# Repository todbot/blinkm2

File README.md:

blinkm_mk2
==========

## aka. BlinkM2, aka BlinkM as WS2812 / NeoPixel controller

### Key Features
* WS2812 / NeoPixel controller (of at least 16 pixels)
* On-board LEDs (maybe two or more)
* Small! (< 1 inch square)
* Stand-alone operation, as original BlinkM
* Inputs for controlling behavior
* Turn into tiny Arduino! (attiny85, attiny84)
* Default firmware is just Arduino sketch (uses awesome ATtinyCore)

### How is this different from blink(1) USB RGB LED?
* blink(1) is retail product, not programmable, tied to a computer, with more robust USB stack
* BlinkM2 / BlinkM Neo is a tiny Arduino, meant to work stand-alone

### Some future directions
* Connector for additional Neopixel LEDs (not just pads)
* USB-based? NO (Micronuclues bootloader, like Digispark), NOT I2C? (but could use A0)
* Serial as well as I2C?  Maybe with SoftSerial
* Should on-board LEDs be in-line or parallel to off-board?
* Can we switch them? (Need more pins then, no ATtiny85)
- Digispark based?
- events trigger patterns:
- CapSense using "ADCTouch" library  (can this work on ATtiny84/85 system?)
- put inbound resistor on inputs for protection?

### Notes:
- TinyTouchLib works on Digispark (ATtiny85 at 16.5MHZ), with light editing. See TinyTouchTest1 sketch

### Further Reading:
- See also PatternIdeas.md

-
-

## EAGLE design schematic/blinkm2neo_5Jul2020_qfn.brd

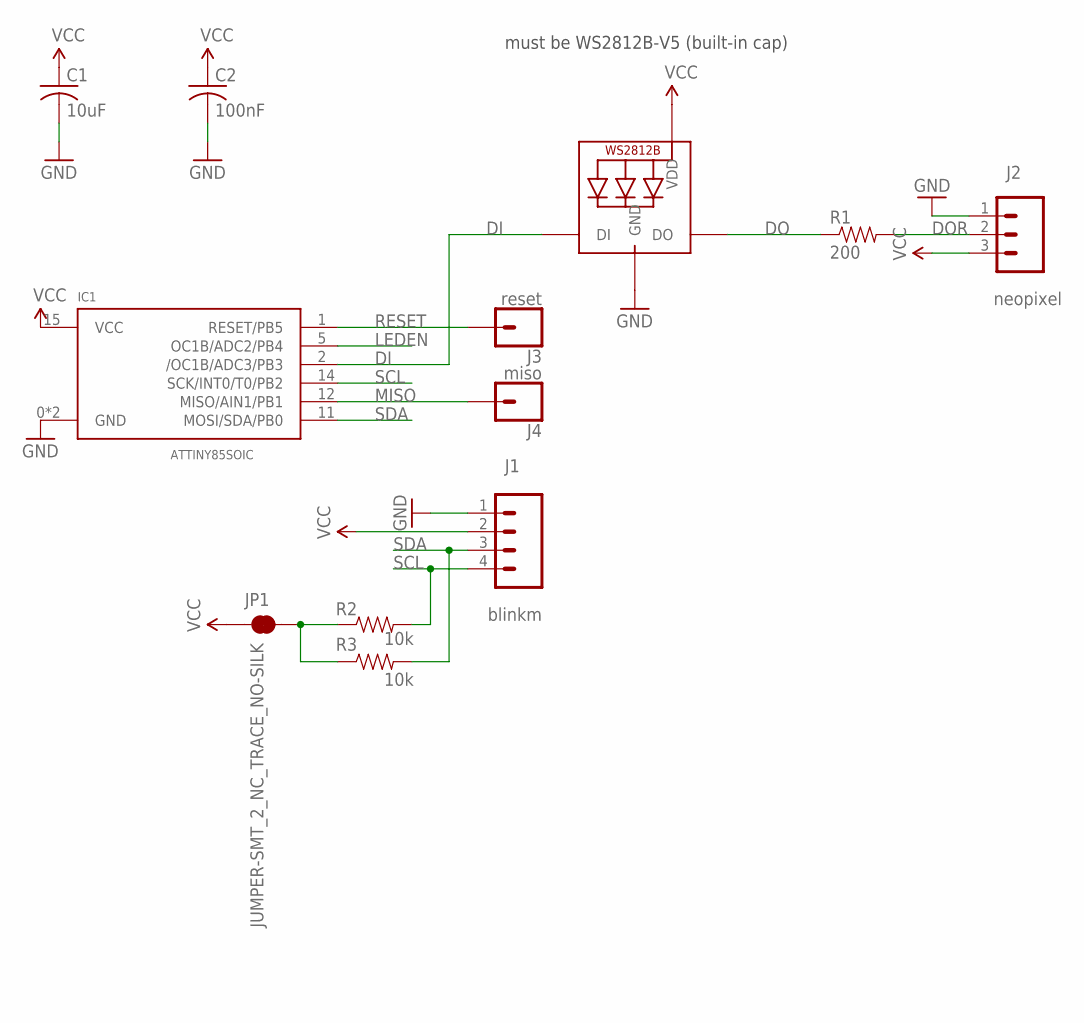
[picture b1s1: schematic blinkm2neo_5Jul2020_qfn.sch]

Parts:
C1: 10uF; C0402
C2: 100nF; C0402
IC1: ATTINY85SOIC; QFN20
J1: blinkm; 1X04
J2: neopixel; 1X03
J3: reset; 1X01_NO_SILK
J4: miso; 1X01_NO_SILK
JP1: JUMPER-SMT_2_NC_TRACE_NO-SILK; SMT-JUMPER_2_NC_TRACE_NO-SILK
LED1: WS2812B-V5; WS2812B
R1: 200; 0402
R2, R3: 10k; 0402

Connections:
DI: IC1.2 (/OC1B/ADC3/PB3), LED1.4-DIN (DI)
DO: LED1.2-DOUT (DO), R1.1
DOR: J2.2, R1.2
GND: C1.2, C2.2, IC1.0 (GND), IC1.8 (GND), J1.1, J2.1, LED1.3-GND (GND)
LEDEN: IC1.5 (OC1B/ADC2/PB4)
MISO: IC1.12 (MISO/AIN1/PB1), J4.1
unnamed: JP1.2, R2.1, R3.1
RESET: IC1.1 (RESET/PB5), J3.1
SCL: IC1.14 (SCK/INT0/T0/PB2), J1.4, R2.2
SDA: IC1.11 (MOSI/SDA/PB0), J1.3, R3.2
VCC: C1.1, C2.1, IC1.15 (VCC), J1.2, J2.3, JP1.1, LED1.1-VDD (VDD)

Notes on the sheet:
must be WS2812B-V5 (built-in cap)

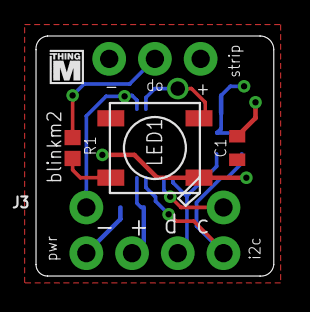
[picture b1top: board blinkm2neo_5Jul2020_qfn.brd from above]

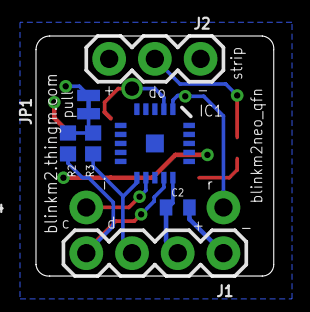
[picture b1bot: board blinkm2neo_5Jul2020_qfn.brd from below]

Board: 2 copper layers, 13.2 x 13.3 mm, 13 parts (8 on the bottom side), 10 nets.

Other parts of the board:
U$1: THINGM_LOGO_0.075IN

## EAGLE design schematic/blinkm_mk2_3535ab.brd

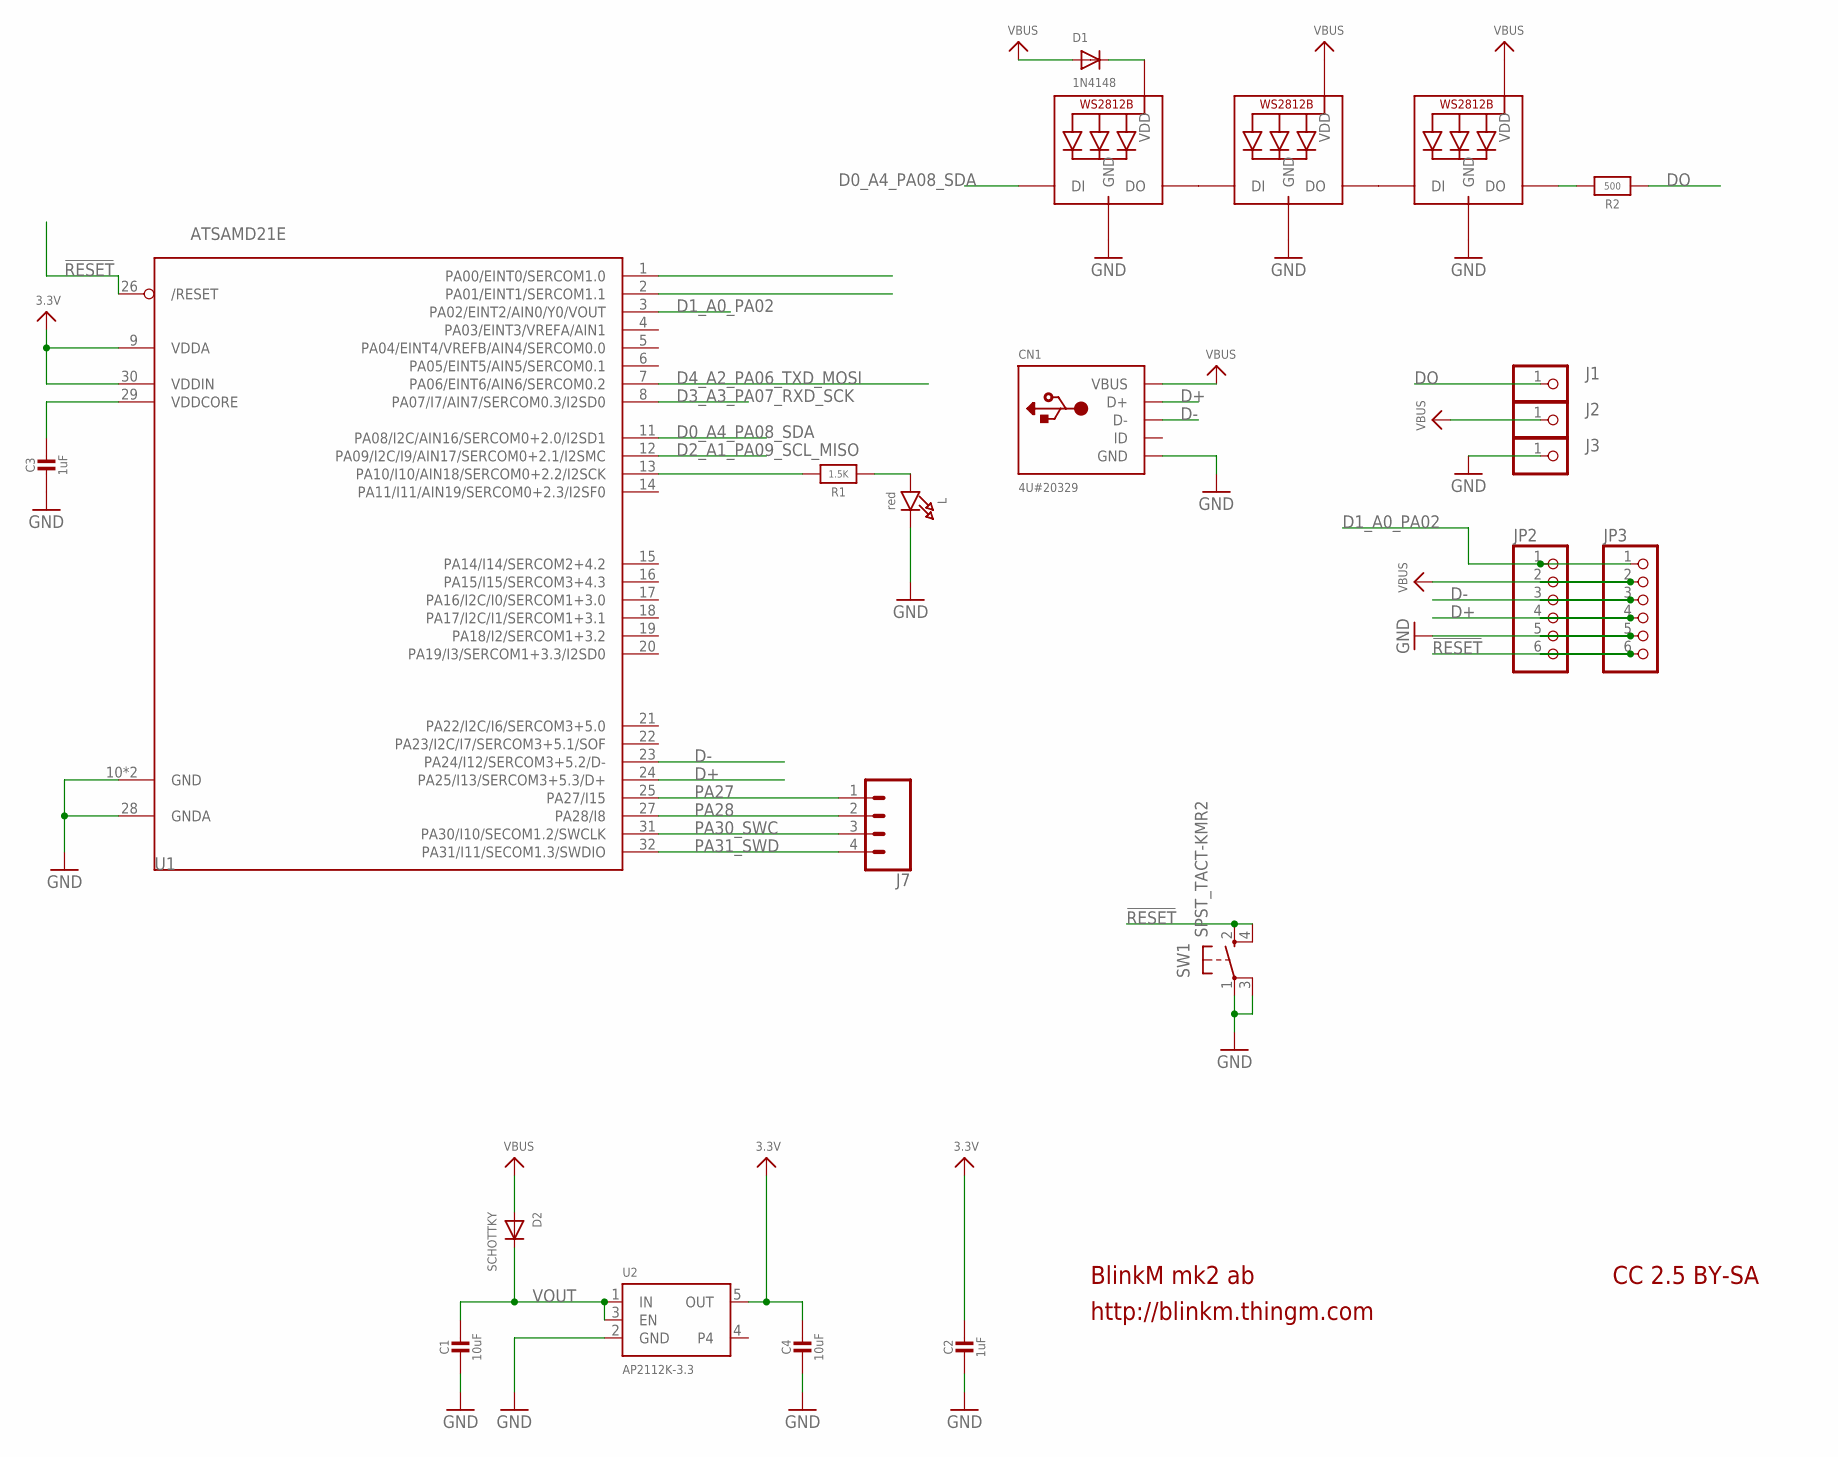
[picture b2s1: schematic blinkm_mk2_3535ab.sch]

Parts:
C1, C4: 10uF; _0402
C2, C3: 1uF; _0402
CN1: 4U#20329; 4UCONN_20329_V2
D1: 1N4148; SOD-523
D2: SCHOTTKY; SOD-523
J1, J2, J3: PINHD-1X1; 1X01
J7: CONN_041X04_NO_SILK; 1X04_NO_SILK
JP2, JP3: PINHD-1X6CLEAN; 1X06-CLEAN
L: red; CHIPLED_0603_NOOUTLINE
L1, L2, L3: WS2812B3535; LED3535
R1: 1.5K; _0402
R2: 500; _0402
SW1: SPST_TACT-KMR2; KMR2
U1: ATSAMD21E; QFN32_5MM
U2: AP2112K-3.3; SOT23-5

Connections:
3.3V: C2.1, C4.1, U1.9 (VDDA), U1.30 (VDDIN), U2.5 (OUT)
!RESET: JP2.6, JP3.6, SW1.2 (S), SW1.4 (S1), U1.26 (/RESET)
A3: U1.1 (PA00/EINT0/SERCOM1.0)
D0_A4_PA08_SDA: L1.1 (DI), U1.11 (PA08/I2C/AIN16/SERCOM0+2.0/I2SD1)
D1_A0_PA02: JP2.1, JP3.1, U1.3 (PA02/EINT2/AIN0/Y0/VOUT)
D2_A1_PA09_SCL_MISO: U1.12 (PA09/I2C/I9/AIN17/SERCOM0+2.1/I2SMC)
D3_A3_PA07_RXD_SCK: U1.8 (PA07/I7/AIN7/SERCOM0.3/I2SD0)
D4_A2_PA06_TXD_MOSI: U1.7 (PA06/EINT6/AIN6/SERCOM0.2)
D+: CN1.D+, JP2.4, JP3.4, U1.24 (PA25/I13/SERCOM3+5.3/D+)
D-: CN1.D-, JP2.3, JP3.3, U1.23 (PA24/I12/SERCOM3+5.2/D-)
DO: J1.1, R2.1
GND: C1.2, C2.2, C3.2, C4.2, CN1.BASE@1 (GND), CN1.BASE@2 (GND), CN1.GND, CN1.SPRT@1 (GND), CN1.SPRT@2 (GND), CN1.SPRT@3 (GND), CN1.SPRT@4 (GND), J3.1, JP2.5, JP3.5, L.C, L1.4 (GND), L2.4 (GND), L3.4 (GND), SW1.1, SW1.3 (P1), U1.10 (GND), U1.28 (GNDA), U1.33 (GND), U2.2 (GND)
unnamed: L.A, R1.1
unnamed: R1.2, U1.13 (PA10/I10/AIN18/SERCOM0+2.2/I2SCK)
unnamed: L1.3 (DO), L2.1 (DI)
unnamed: L3.3 (DO), R2.2
unnamed: L2.3 (DO), L3.1 (DI)
unnamed: D1.K (C), L1.2 (VDD)
PA27: J7.1, U1.25 (PA27/I15)
PA28: J7.2, U1.27 (PA28/I8)
PA30_SWC: J7.3, U1.31 (PA30/I10/SECOM1.2/SWCLK)
PA31_SWD: J7.4, U1.32 (PA31/I11/SECOM1.3/SWDIO)
VBUS: CN1.VBUS, D1.A, D2.A, J2.1, JP2.2, JP3.2, L2.2 (VDD), L3.2 (VDD)
VDDCORE: C3.1, U1.29 (VDDCORE)
VOUT: C1.1, D2.K (C), U2.1 (IN), U2.3 (EN)

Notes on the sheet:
BlinkM mk2 ab
http://blinkm.thingm.com
CC 2.5 BY-SA

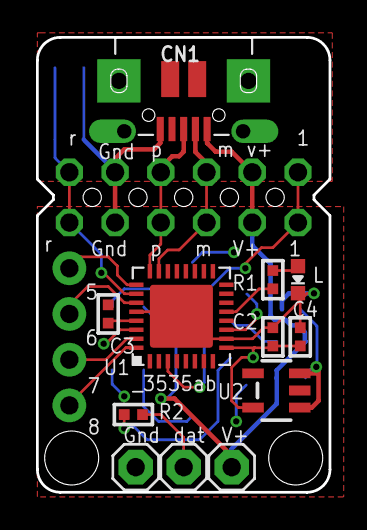
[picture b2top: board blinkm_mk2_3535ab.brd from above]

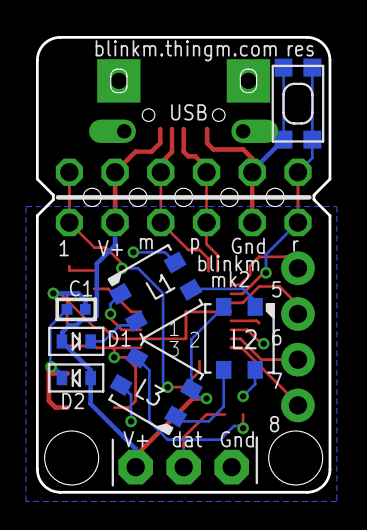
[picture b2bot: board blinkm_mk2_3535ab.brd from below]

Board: 2 copper layers, 16.3 x 25.3 mm, 22 parts (7 on the bottom side), 21 nets.

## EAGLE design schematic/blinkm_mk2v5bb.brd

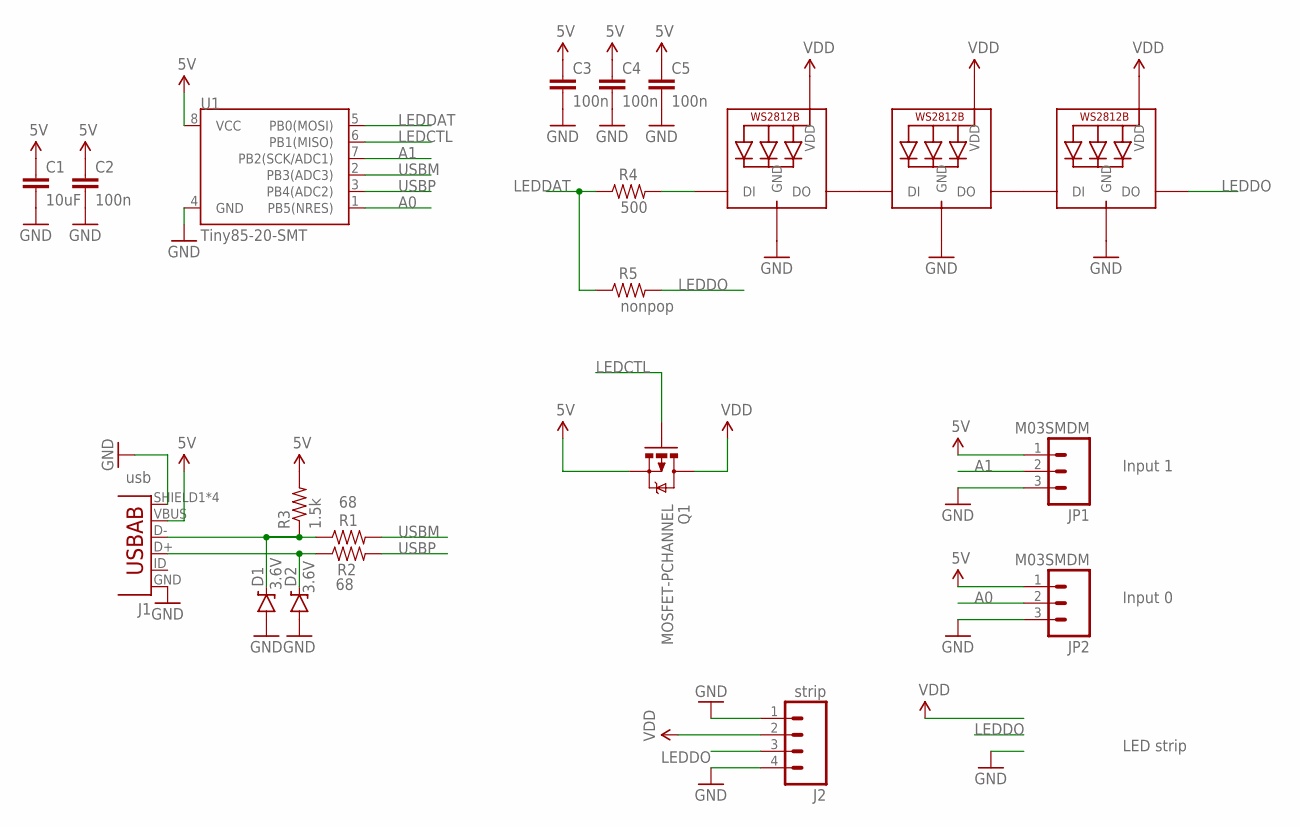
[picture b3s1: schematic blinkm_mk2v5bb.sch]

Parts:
C1: 10uF; 0603-CAP
C2, C3, C4, C5: 100n; 0603-CAP
D1, D2: 3.6V; SOD-323
J1: usb; USB-AB-MICRO-SMD
J2: strip; 1X04_NO_SILK_ALL_ROUND
JP1, JP2: M03SMDM; 1X03-SMD-MINIMAL
LED1, LED2, LED3: WS2812B3535; LED3535
Q1: MOSFET-PCHANNEL; SOT23-3
R1, R2: 68; 0603-RES
R3: 1.5k; 0603-RES
R4: 500; 0603-RES
R5: nonpop; 0603-RES
U1: Tiny85-20-SMT; SO08-EIAJ

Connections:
5V: C1.1, C2.1, C3.1, C4.1, C5.1, J1.VBUS, JP1.1, JP2.1, Q1.2 (S), R3.2, U1.8 (VCC)
A0: JP2.2, U1.1 (PB5(NRES))
A1: JP1.2, U1.7 (PB2(SCK/ADC1))
GND: C1.2, C2.2, C3.2, C4.2, C5.2, D1.A, D2.A, J1.GND, J1.SHIELD1 (SHIELD), J1.SHIELD2 (SHIELD), J1.SHIELD3 (SHIELD), J1.SHIELD4 (SHIELD), J2.1, J2.4, JP1.3, JP2.3, LED1.4 (GND), LED2.4 (GND), LED3.4 (GND), U1.4 (GND)
LEDCTL: Q1.1 (G), U1.6 (PB1(MISO))
LEDDAT: R4.1, R5.1, U1.5 (PB0(MOSI))
LEDDO: J2.3, LED3.3 (DO), R5.2
unnamed: LED1.3 (DO), LED2.1 (DI)
unnamed: LED2.3 (DO), LED3.1 (DI)
unnamed: D1.C, J1.D-, R1.1, R3.1
unnamed: D2.C, J1.D+, R2.1
unnamed: LED1.1 (DI), R4.2
USBM: R1.2, U1.2 (PB3(ADC3))
USBP: R2.2, U1.3 (PB4(ADC2))
VDD: J2.2, LED1.2 (VDD), LED2.2 (VDD), LED3.2 (VDD), Q1.3 (D)

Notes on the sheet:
Input 1
Input 0
LED strip

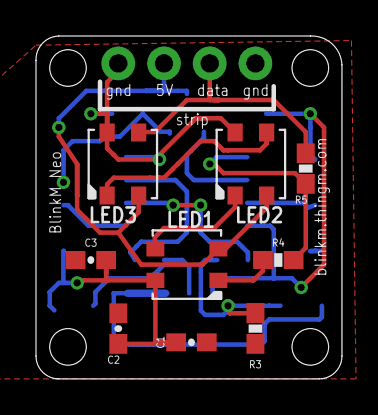
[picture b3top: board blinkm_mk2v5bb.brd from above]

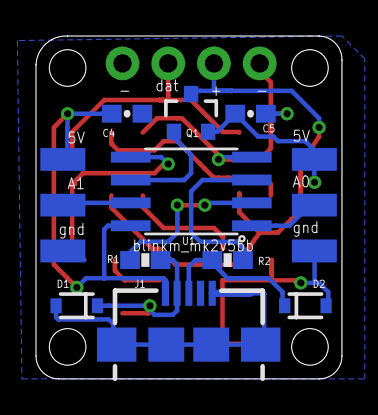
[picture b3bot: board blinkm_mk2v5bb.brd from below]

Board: 2 copper layers, 17.0 x 19.1 mm, 21 parts (11 on the bottom side), 15 nets.

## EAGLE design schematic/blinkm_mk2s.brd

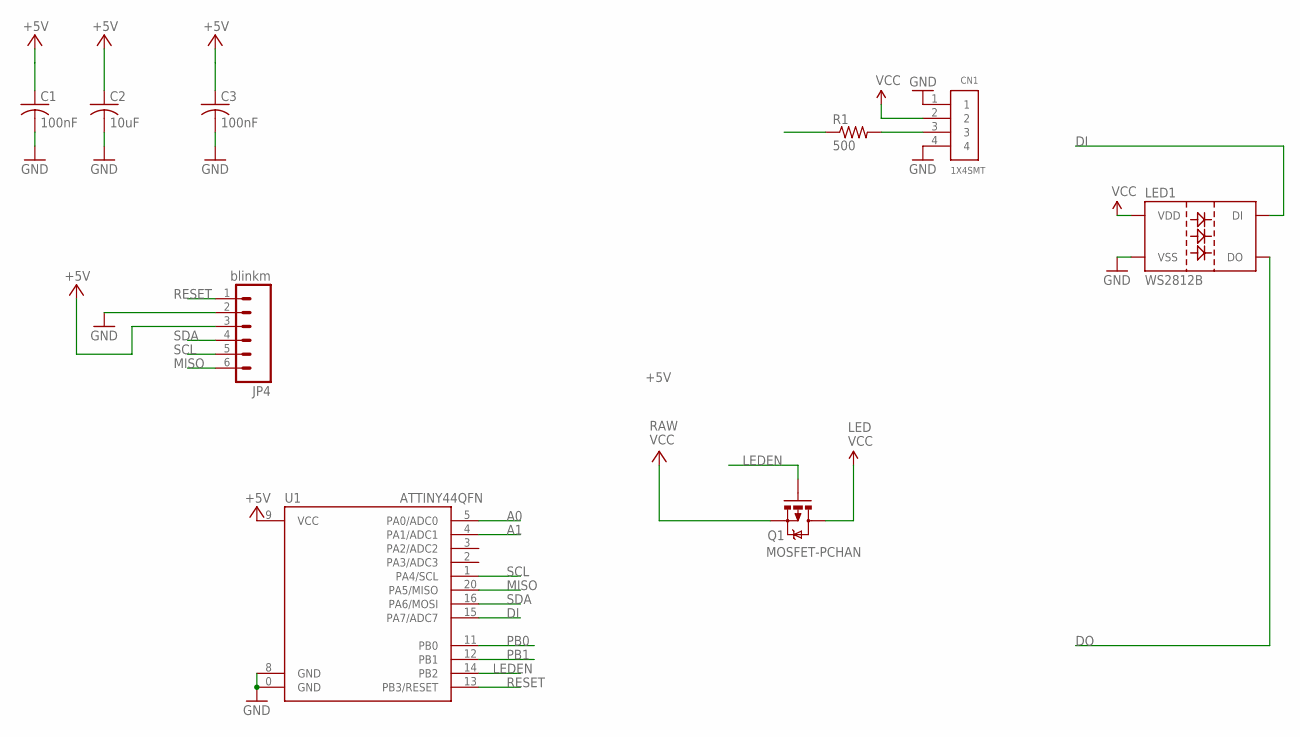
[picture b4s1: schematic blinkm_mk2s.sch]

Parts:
C1, C3: 100nF; C0603
C2: 10uF; C0603
CN1: 1X4SMT; 1X4-SMT
JP4: blinkm; 1X06_LOCK
LED1: WS2812B
Q1: MOSFET-PCHAN; SOT23-3
R1: 500; 0603-RES
U1: ATTINY44QFN; QFN20

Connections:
+5V: C1.1, C2.1, C3.1, JP4.3, Q1.2 (S), U1.9 (VCC)
A0: U1.5 (PA0/ADC0)
A1: U1.4 (PA1/ADC1)
DI: LED1.4 (DI), U1.15 (PA7/ADC7)
DO: LED1.2 (DO), R1.1
GND: C1.2, C2.2, C3.2, CN1.1, CN1.4, JP4.2, LED1.3 (VSS), U1.0 (GND), U1.8 (GND)
LEDEN: Q1.1 (G), U1.14 (PB2)
MISO: JP4.6, U1.20 (PA5/MISO)
unnamed: CN1.3, R1.2
PB0: U1.11 (PB0)
PB1: U1.12 (PB1)
RESET: JP4.1, U1.13 (PB3/RESET)
SCL: JP4.5, U1.1 (PA4/SCL)
SDA: JP4.4, U1.16 (PA6/MOSI)
VCC: CN1.2, LED1.1 (VDD), Q1.3 (D)

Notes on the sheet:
LED
VCC
RAW

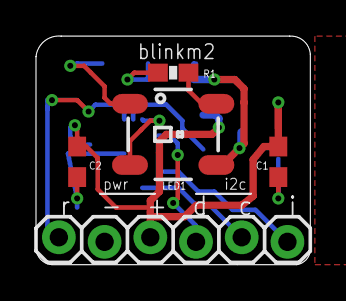
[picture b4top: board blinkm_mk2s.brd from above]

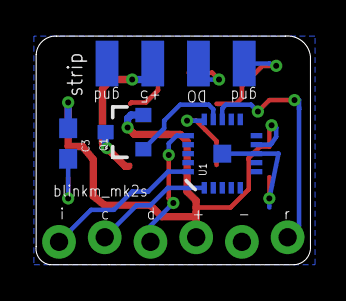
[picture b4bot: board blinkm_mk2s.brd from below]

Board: 2 copper layers, 15.2 x 12.7 mm, 9 parts (4 on the bottom side), 11 nets.

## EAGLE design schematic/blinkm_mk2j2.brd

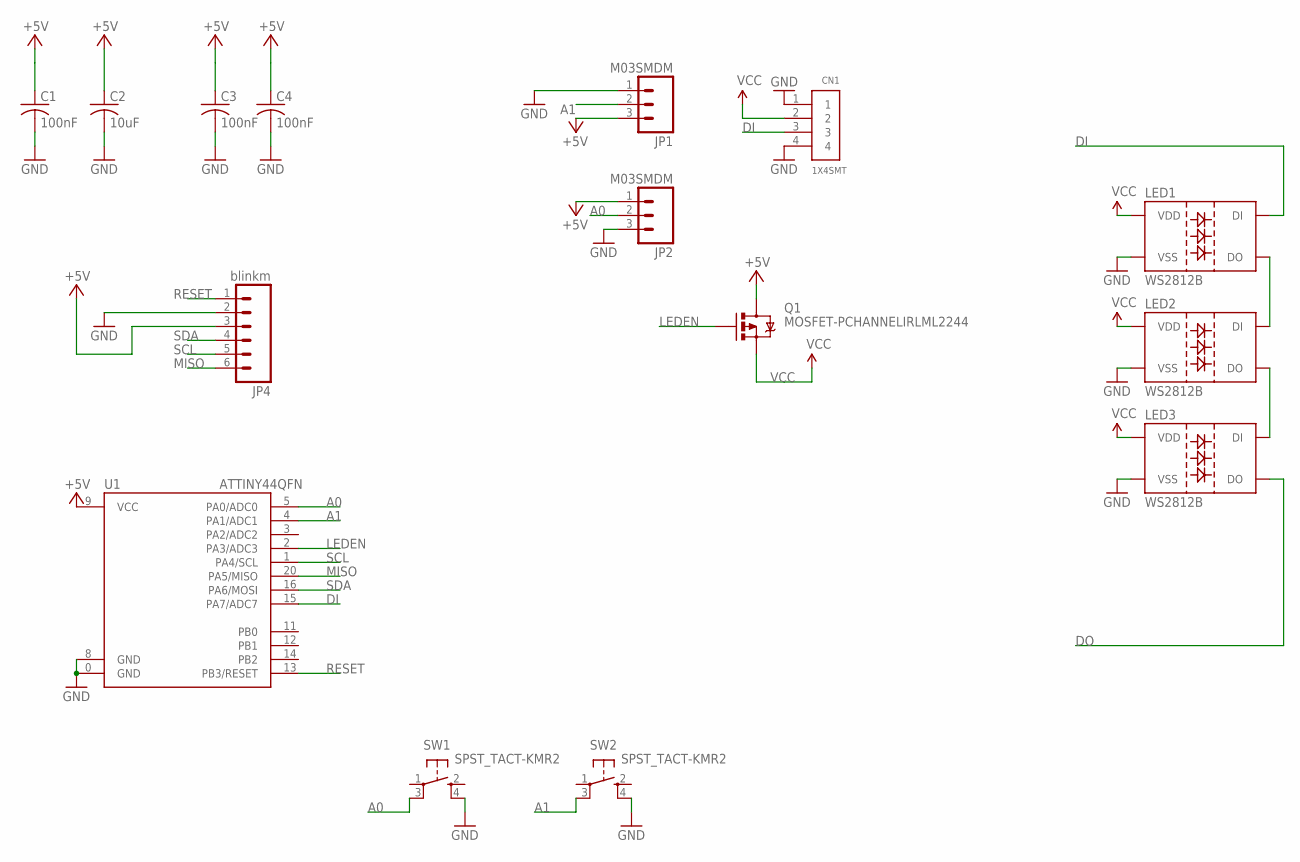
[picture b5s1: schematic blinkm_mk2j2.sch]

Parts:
C1, C3, C4: 100nF; C0603
C2: 10uF; C0603
CN1: 1X4SMT; 1X4-SMT
JP1, JP2: M03SMDM; 1X03-SMD-MINIMAL
JP4: blinkm; 1X06_LOCK
LED1, LED2, LED3: WS2812B
Q1: MOSFET-PCHANNELIRLML2244; SOT23-3
SW1, SW2: SPST_TACT-KMR2; KMR2
U1: ATTINY44QFN; QFN20

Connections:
+5V: C1.1, C2.1, C3.1, C4.1, JP1.3, JP2.1, JP4.3, Q1.3 (D), U1.9 (VCC)
A0: JP2.2, SW1.3 (P1), U1.5 (PA0/ADC0)
A1: JP1.2, SW2.3 (P1), U1.4 (PA1/ADC1)
DI: CN1.3, LED1.4 (DI), U1.15 (PA7/ADC7)
DO: LED3.2 (DO)
DOI1: LED1.2 (DO), LED2.4 (DI)
DOI2: LED2.2 (DO), LED3.4 (DI)
GND: C1.2, C2.2, C3.2, C4.2, CN1.1, CN1.4, JP1.1, JP2.3, JP4.2, LED1.3 (VSS), LED2.3 (VSS), LED3.3 (VSS), SW1.4 (S1), SW2.4 (S1), U1.0 (GND), U1.8 (GND)
LEDEN: Q1.1 (G), U1.2 (PA3/ADC3)
MISO: JP4.6, U1.20 (PA5/MISO)
RESET: JP4.1, U1.13 (PB3/RESET)
SCL: JP4.5, U1.1 (PA4/SCL)
SDA: JP4.4, U1.16 (PA6/MOSI)
VCC: CN1.2, LED1.1 (VDD), LED2.1 (VDD), LED3.1 (VDD), Q1.2 (S)

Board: 2 copper layers, 15 parts (8 on the bottom side), 13 nets, no tracks yet.

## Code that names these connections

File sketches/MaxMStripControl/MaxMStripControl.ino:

 /**
  * MaxMStripContorl -- 
  *
  * Some code take from TinyWireM/examples
  *
  * More on TinyWireS usage - see TinyWireS.h
  */

#include "TinyWireS.h"                  // wrapper class for I2C slave routines

#include "light_ws2812.h"


// BlinkM MaxM pins (see below for where this came from)
const int redPin = 8;   // PB2 OC0A
const int grnPin = 7;   // PA7 OC0B
const int bluPin = 5;   // PA5 OC1B
const int sdaPin = 6;   // PA6 
const int sclPin = 9;   // PA4
const int in0Pin = A0;  // PA0
const int in1Pin = A1;  // PA1
const int in2Pin = A2;  // PA2
const int in3Pin = A3;  // PA3

// From: blinkm/variants/tiny14/pins_arduino.h  
// (originally from: http://hlt.media.mit.edu/?p=1695 )
// ATMEL ATTINY84 / ARDUINO
//
//                           +-\/-+
//                     VCC  1|    |14  GND
//             (D 10)  PB0  2|    |13  AREF (D  0)
//             (D  9)  PB1  3|    |12  PA1  (D  1) 
//                     PB3  4|    |11  PA2  (D  2) 
//  PWM  INT0  (D  8)  PB2  5|    |10  PA3  (D  3) 
//  PWM        (D  7)  PA7  6|    |9   PA4  (D  4) 
//  PWM        (D  6)  PA6  7|    |8   PA5  (D  5)        PWM
//                           +----+

const int I2C_SLAVE_ADDR  = 0x09;     // default BlinkM addr

const int NUM_LEDS = 8;

typedef struct CRGB_ { uint8_t g; uint8_t r; uint8_t b; } CRGB;
CRGB leds[1]; //NUM_LEDS];


void setup()
{
  TinyWireS.begin(I2C_SLAVE_ADDR); 
  
  leds[0].r=32; leds[0].g=32; leds[0].b=32;

  ws2812_sendarray( (uint8_t*)leds, 3 );
  delay(500);
  
  pinMode( redPin, OUTPUT);   
  pinMode( grnPin, OUTPUT);  
  pinMode( bluPin, OUTPUT);  
  blink( redPin,1);
  blink( grnPin,1);
  blink( bluPin,1);

}

void loop()
{
  byte cmd;
  byte r,g,b;

  if( TinyWireS.available() ) { 

    cmd = TinyWireS.receive();    // first byte is command
    if( cmd == 'c' ) { 
      r = TinyWireS.receive();
      g = TinyWireS.receive();
      b = TinyWireS.receive();
      analogWrite( redPin, r );
      analogWrite( grnPin, g );
      analogWrite( bluPin, b );

    }
    // else if( cmd == 'h' ) { 
    //}
    else {
    }
  }
}


//
void blink(byte pin, byte times)
{ 
  for (byte i=0; i< times; i++){
    digitalWrite(pin,HIGH);
    delay (200);
    digitalWrite(pin,LOW);
    delay (100);
  }
}

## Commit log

2013-06-05 added some files
2014-01-02 added blinkm_mk2c board idea
2014-01-02 updated blinkm_mk2c board layout, fully routed
2014-01-24 sync
2014-01-26 sigh
2014-01-30 added cpptsts to make new fader logic
2014-01-30 using new ledfader
2014-02-01 added BTBlinkMmk2 to test blinkm algos on blinkytape
2014-02-01 more better
2014-02-02 got basic fade and pattern playing logic working on attiny84
2014-02-05 made it simpler, oy.
2014-02-06 almost working, too much ram usage tho
2014-02-06 moved to light_ws2812, saved 180 bytes
2014-02-07 more progress
2014-02-07 hsv kinda working
2014-02-14 more pcb layout ideas, more firmware
2014-03-30 sync up before move
2015-05-05 added semi-working apr2015
2015-05-10 added blinkmmk22apr2015
2015-05-10 fixed
2015-05-11 fixed more
2015-05-13 adding commands to patterns, playing with static funcs
2015-05-23 added newest thinking
2015-06-07 trying out new fw_algo_tests stuff
2015-06-08 wooo new algo maybe sorta works kinda
2015-06-08 had to move led_fader functions back to header file because of Arduino compile limitations (cannot use Serial.print() in other C file)
2015-06-11 first light on led pattern chooser
2015-06-12 added new ledn patterns
2015-06-18 added mk2r schem
2015-06-22 woot, hopefully figured out smaller algo for fading
2015-07-13 blinkm2_light added
2015-07-14 added single-led blinkm2 idea
2015-07-15 blinkm2_light added patterns
2015-07-16 blinkm2_light added brightness
2015-07-21 blinkm2_light pattern led rotation thinking coming together
2015-07-24 blinkm2_light rotate first light
2015-07-26 blinkm2_light gosub play works sorta, but not at end of script
2015-07-26 blinkm2_light: oops forgot to check in some stuff
2015-07-26 added misc other bits
2015-07-30 update before sketching15
2016-07-18 added digispark-inspired usb-based blinkm neo idea
2016-07-21 another usb-based idea
2016-07-21 thoughts on touch-sensors
2019-01-24 added _3535aa,ab ideas
2020-07-06 added BlinkM2_Jul2020
2020-07-08 more progress on BlinkM2_Jul2020
2020-07-08 BlinkM2_Jul2020 reading scripts from flash correctly
2020-07-26 verified working-ish on ATtiny85
2020-07-31 updated ATtiny version to use standard Wire I2C events
2020-07-31 some potential BlinkM2 designs
2020-07-31 update readme a little
2020-08-01 added pullup resistors
2020-08-04 eeprom reset and general eeprom read/write mostly worknig
2020-08-04 utils in their own file now
2020-08-04 rework eeprom handling to struct
2020-08-05 add in "L" functionality, partially
2020-08-06 eeprom struct and eeprom protection

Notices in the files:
parts and their libraries:
SparkFun-Connectors: Licensing: CC v3.0 Share-Alike You are welcome to use this library for commercial purposes.
SparkFun-Connectors: Licensing: Creative Commons ShareAlike 4.0 International - https://creativecommons.org/licenses/by-sa/4.0
